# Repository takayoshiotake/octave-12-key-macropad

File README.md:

# Octave

[![CC BY-SA 4.0][cc-by-sa-shield]][cc-by-sa]

The Octave is a 12-key macropad.
It is primarily designed to be a compact keyboard with support for 12 function keys (F1 - F12).

## Status

- [x] prototype-3.1: Upgrade with LEDs under keys
  - [x] LED Animation
  - [x] PCB: OK!
- [x] prototype-3: Simple design
  - [x] Enclosure: OK!
  - [x] Test: OK!
  - [x] PCB: OK!
- [x] prototype-2: Custom MCU board
  - [x] Consideration
  - [x] Test
  - [x] PCB
- [x] prototype-1

## Specifications

- USB-C (USB2.0, HID)
  - 🔗 <https://pid.codes/1209/8CAE/>
- Hot-swap sockets for MX compatible switches
- Programmable firmware (CircuitPython)

## Layout

📄 [layout/keyboard-layout.png](layout/keyboard-layout.png) (rev.6)

- 12 function keys (F1 - F12)

**RAW data for Keyboard Layout Editor v0.15:**

📄 [layout/keyboard-layout.rawdata.json](layout/keyboard-layout.rawdata.json)

```json
[{f:3},"F1\nF9","F2\nF10","F3\nF11","F4\nF12"],
["F5\nVol-","F6\nVol+","F7\nRW","F8\nFF"],
["Shift","Ctrl","Esc\nLED","MO(1)"]
```

- 🔗 [Keyboard Layout Editor](http://www.keyboard-layout-editor.com/)

## Schematic

📄 [electronics/Octave_Input_PCB.svg](electronics/Octave_Input_PCB.svg) (rev.6.1.2)

I have also designed a custom MCU circuit from prototype-2, the MCU is RP2040 and the software runs on CircuitPython built specifically for it.

📄 [electronics/Octave_Input_PCB/Octave_Input_PCB.kicad_sch](electronics/Octave_Input_PCB/Octave_Input_PCB.kicad_sch)

### Upgrade schematic with LEDs under keys

📄 [electronics/Octave_Input_LED_PCB.svg](electronics/Octave_Input_LED_PCB.svg) (rev.1.0.0)

📄 [electronics/Octave_Input_PCB/Octave_Input_LED_PCB.kicad_sch](electronics/Octave_Input_PCB/Octave_Input_LED_PCB.kicad_sch)

## PCB

📄 [electronics/Octave_Input_PCB_3D.png](electronics/Octave_Input_PCB_3D.png) (rev.6.1.3)

📄 [electronics/Octave_Input_PCB/Octave_Input_PCB.kicad_pcb](electronics/Octave_Input_PCB/Octave_Input_PCB.kicad_pcb)

### Upgrade PCB with LEDs under keys

📄 [electronics/Octave_Input_LED_PCB_3D.png](electronics/Octave_Input_LED_PCB_3D.png) (rev.1.0.0)

📄 [electronics/Octave_Input_LED_PCB/Octave_Input_LED_PCB.kicad_pcb](electronics/Octave_Input_LED_PCB/Octave_Input_LED_PCB.kicad_pcb)

## CircuitPython

Software for the Octave (prototype-2, prototype-3) runs on CircuitPython.

**Latest:**

- 🔗 [adafruit/circuitpython](https://github.com/adafruit/circuitpython)
  - 🔗 <https://github.com/adafruit/circuitpython/tree/main/ports/raspberrypi/boards/takayoshiotake_octave_rp2040>
- 🔗 [Built UF2](https://adafruit-circuit-python.s3.amazonaws.com/index.html?prefix=bin/takayoshiotake_octave_rp2040/)

**Older:**

- 🔗 [takayoshiotake/circuitpython:7.3.x-board-octave-rp2040](https://github.com/takayoshiotake/circuitpython/tree/7.3.x-board-octave-rp2040)
  - 🔗 <https://github.com/takayoshiotake/circuitpython/tree/c3b4d05dc04d74c6229506215eae799fb23f37ce/ports/raspberrypi/boards/takayoshiotake_octave_rp2040>

- How to build:
  - 🔗 <https://learn.adafruit.com/building-circuitpython/build-circuitpython>
  - 🔗 <https://github.com/takayoshiotake/circuitpython/blob/c3b4d05dc04d74c6229506215eae799fb23f37ce/BUILDING.md>

## Plate

📄 [mechanics/Octave_Plate_3D.png](mechanics/Octave_Plate_3D.png) (rev.1.0.3)

📄 [mechanics/Octave_Plate/Octave_Plate.kicad_pcb](mechanics/Octave_Plate/Octave_Plate.kicad_pcb)

## Enclosure

- 📄 [mechanics/Octave_Enclosure-Case.stl](mechanics/Octave_Enclosure-Case.stl) (rev.1.0.0)
- 📄 [mechanics/Octave_Enclosure-Top Frame.stl](mechanics/Octave_Enclosure-Top%20Frame.stl) (rev.1.0.0)

## BOM & Software

🏷 [prototype-3-pcb](https://github.com/takayoshiotake/octave-12-key-macropad/releases/tag/prototype-3-pcb)

| Material | Unit | Designator | Note | JLCPCB Part # |
|-|-:|-|-|-|
| Octave CPU PCB rev.6.1.3 | 1 | n/a | JLCPCB |
| Octave Input PCB rev.6.1.3 *[2]* | 1 | n/a | JLCPCB |
| Octave Plate rev.1.0.3 | 1 | n/a | JLCPCB, Alminium PCB (t=1.6mm) |
| 0151660120 | 1 | n/a | Molex 0.50mm pitch FFC, Type D, 50.80mm, 12 circuits |
| CPG151101S11-2 | 12 | SW1-12 *[2]* | Kailh®︎ hot swap socket (White) |
||
| Octave Enclosure Case rev.1.0.0 | 1 | n/a | JLCPCB, 3D printing (MJF), PA12-HP Nylon |
| Octave Enclosure Top Frame rev.1.0.0 | 1 | n/a | JLCPCB, 3D printing (MJF), PA12-HP Nylon |
| PORON | 4 | n/a | 78mm x 2.5mm (t=1.5mm) |
| PORON | 4 | n/a | 59mm x 2.5mm (t=1.5mm) |
| Screw M2 5mm | 1 | n/a | Hirosugi B-0205 |
| Screw M2 8mm | 4 | n/a | Hirosugi B-0208 |
| Insert nut M2 | 4 | n/a | Hirosugi HSB-203030Z |
| Nut M2 | 1 | n/a | Hirosugi BNT-02-2 |
| Washer M2 | 1 | n/a | Hirosugi BW-0243-03 |
||
| 30pF 0402 | 2 | C15, C16 | PCBA | C1570 |
| 100nF 0402 | 10 | C5-14 | PCBA | C307331 |
| 1uF 0402 | 2 | C3, C4 | PCBA | C52923 |
| 10uF 0402 | 2 | C1, C2 | PCBA | C15525 |
| 1N4148WS | 12 | D1-12 *[2]* | PCBA | C2128 |
| HRO_TYPE-C-31-M-12 | 1 | J1 | PCBA, USB Connector (Type-C) | C165948 |
| JUSHUO_AFC01-S12FCC-00 | 2 | J2, J3 *[2]* | PCBA, FFC Connector (0.50mm pitch, 12 circuits) | C262268 |
| 27Ω 0402 | 2 | R3, R4 | PCBA | C352446 |
| 1KΩ 0402 | 2 | R7, R8 | PCBA | C11702 |
| 5.1KΩ 0402 | 2 | R1, R2 | PCBA | C25905 |
| 10KΩ 0402 | 2 | R5, R6 | PCBA | C25744 |
| AP2112K-3.3 | 1 | U1 | PCBA | C51118 |
| Raspberry Pi RP2040 | 1 | U2 | PCBA | C2040 |
| W25Q64JVSSIQ | 1 | U3 | PCBA | C179171 |
| 12MHz Crystal Resonator SMD-3225 | 1 | Y1 | PCBA, YSX221SL | C9002 |
| SKRPANE010 | 2 | SW21, SW22 | PCBA, Alps Alpine tactile switch | C470426 |
||
| WS2812C-2020-V1 | 1 | LED1 *[1]* | PCBA, NeoPixel | C2976072 |

MEMO: *[1]* To reduce costs, I did not assemble LED1 with PCBA.
MEMO: *[2]* Can be replaced with upgrade parts.

Upgrade parts:

| Material | Unit | Designator | Note | JLCPCB Part # |
|-|-:|-|-|-|
| Octave Input LED PCB rev.1.0.0 | 1 | n/a | JLCPCB |
| CPG151101S11-2 | 12 | SW1-12 | Kailh®︎ hot swap socket (White) |
||
| 1N4148WS | 12 | D1-12 | PCBA | C2128 |
| JUSHUO_AFC01-S12FCC-00 | 1 | J3 | PCBA, FFC Connector (0.50mm pitch, 12 circuits) | C262268 |
||
| WS2812B-Mini-V3 | 12 | LED201-0212 | NeoPixel |

- Octave CPU PCB rev.6.1.3, Octave Input PCB rev.6.1.3 (PCBA)

- Octave Input LED PCB rev.1.0.0 (Upgrade)

- Octave Plate rev.1.0.3

- Assembly

### Software

- [Software](software/README.md)

### History

- [[Closed] prototype-2](prototype-2/README.md)
- [[Closed] prototype-1](prototype-1/README.md)

## License

This work is licensed under a
[Creative Commons Attribution-ShareAlike 4.0 International License][cc-by-sa].

[![CC BY-SA 4.0][cc-by-sa-image]][cc-by-sa]

[cc-by-sa]: http://creativecommons.org/licenses/by-sa/4.0/
[cc-by-sa-image]: https://licensebuttons.net/l/by-sa/4.0/88x31.png
[cc-by-sa-shield]: https://img.shields.io/badge/license-CC%20BY--SA%204.0-lightgrey.svg

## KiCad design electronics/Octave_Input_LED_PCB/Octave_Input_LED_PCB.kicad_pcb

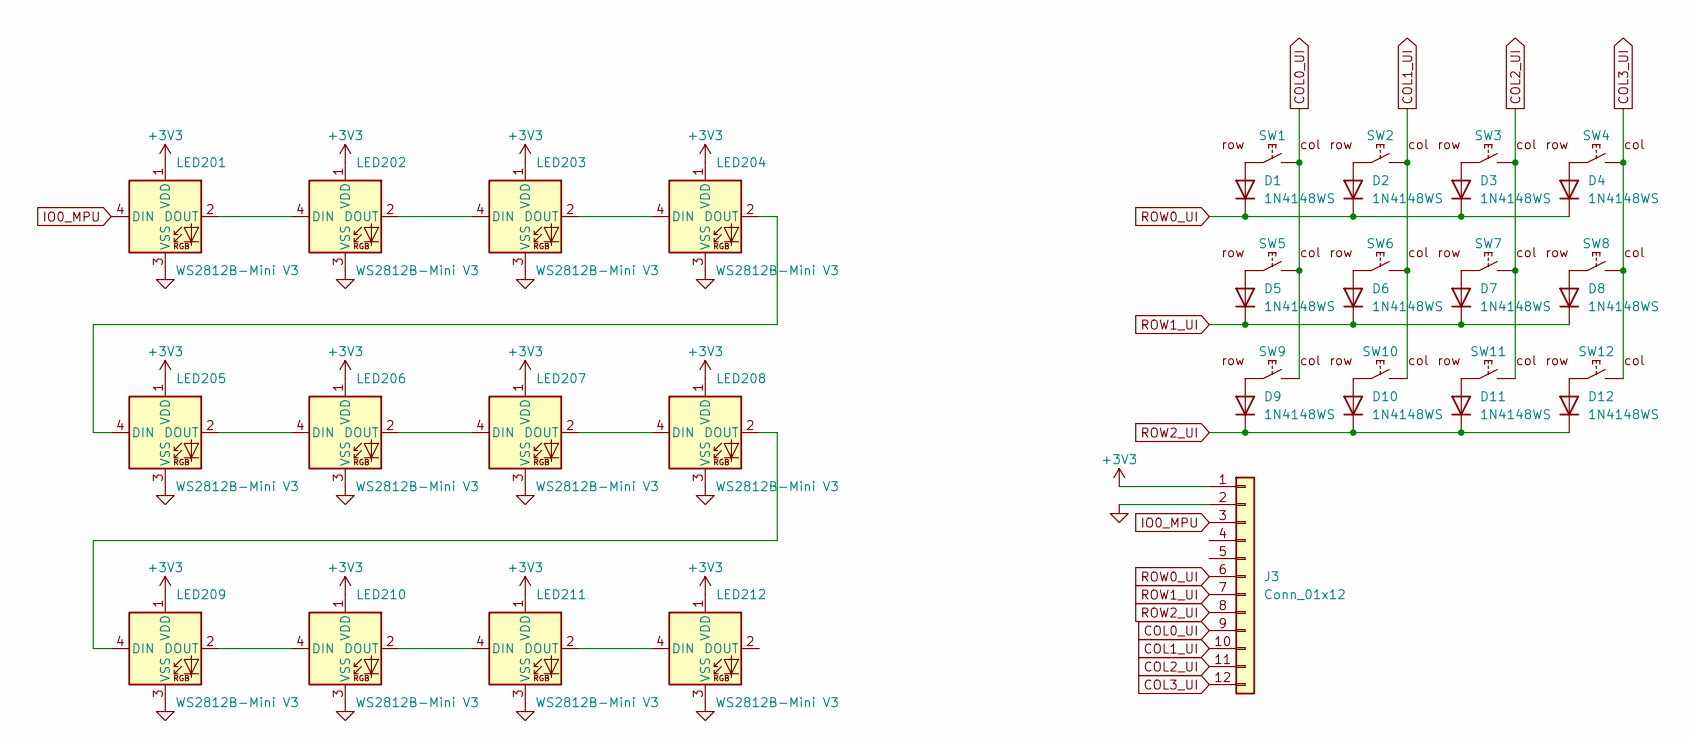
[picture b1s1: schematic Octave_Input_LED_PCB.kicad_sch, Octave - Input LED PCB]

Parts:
D1, D2, D3, D4, D5, D6, D7, D8, D9, D10, D11, D12: 1N4148WS; D_SOD-323F
J3: Conn_01x12; JUSHUO_AFC01-S12FCC-00
LED201, LED202, LED203, LED204, LED205, LED206, LED207, LED208, LED209, LED210, LED211, LED212: WS2812B-Mini V3; WS2812B-Mini_Inverted
SW1, SW2, SW3, SW4, SW5, SW6, SW7, SW8, SW9, SW10, SW11, SW12: SW_Hot_Swap_Socket; Hot_Swap_Socket_CPG151101S11

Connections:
+3V3: J3.1, LED201.1 (VDD), LED202.1 (VDD), LED203.1 (VDD), LED204.1 (VDD), LED205.1 (VDD), LED206.1 (VDD), LED207.1 (VDD), LED208.1 (VDD), LED209.1 (VDD), LED210.1 (VDD), LED211.1 (VDD), LED212.1 (VDD)
COL0_UI: J3.9, SW1.2, SW5.2, SW9.2
COL1_UI: J3.10, SW2.2, SW6.2, SW10.2
COL2_UI: J3.11, SW3.2, SW7.2, SW11.2
COL3_UI: J3.12, SW4.2, SW8.2, SW12.2
GND: J3.2, LED201.3 (VSS), LED202.3 (VSS), LED203.3 (VSS), LED204.3 (VSS), LED205.3 (VSS), LED206.3 (VSS), LED207.3 (VSS), LED208.3 (VSS), LED209.3 (VSS), LED210.3 (VSS), LED211.3 (VSS), LED212.3 (VSS)
IO0_MPU: J3.3, LED201.4 (DIN)
unnamed: D1.2 (A), SW1.1
unnamed: D2.2 (A), SW2.1
unnamed: D3.2 (A), SW3.1
unnamed: D4.2 (A), SW4.1
unnamed: D5.2 (A), SW5.1
unnamed: D6.2 (A), SW6.1
unnamed: D7.2 (A), SW7.1
unnamed: D8.2 (A), SW8.1
unnamed: D9.2 (A), SW9.1
unnamed: D10.2 (A), SW10.1
unnamed: D11.2 (A), SW11.1
unnamed: D12.2 (A), SW12.1
unnamed: LED201.2 (DOUT), LED202.4 (DIN)
unnamed: LED202.2 (DOUT), LED203.4 (DIN)
unnamed: LED203.2 (DOUT), LED204.4 (DIN)
unnamed: LED204.2 (DOUT), LED205.4 (DIN)
unnamed: LED205.2 (DOUT), LED206.4 (DIN)
unnamed: LED206.2 (DOUT), LED207.4 (DIN)
unnamed: LED207.2 (DOUT), LED208.4 (DIN)
unnamed: LED208.2 (DOUT), LED209.4 (DIN)
unnamed: LED209.2 (DOUT), LED210.4 (DIN)
unnamed: LED210.2 (DOUT), LED211.4 (DIN)
unnamed: LED211.2 (DOUT), LED212.4 (DIN)
ROW0_UI: D1.1 (K), D2.1 (K), D3.1 (K), D4.1 (K), J3.6
ROW1_UI: D5.1 (K), D6.1 (K), D7.1 (K), D8.1 (K), J3.7
ROW2_UI: D9.1 (K), D10.1 (K), D11.1 (K), D12.1 (K), J3.8

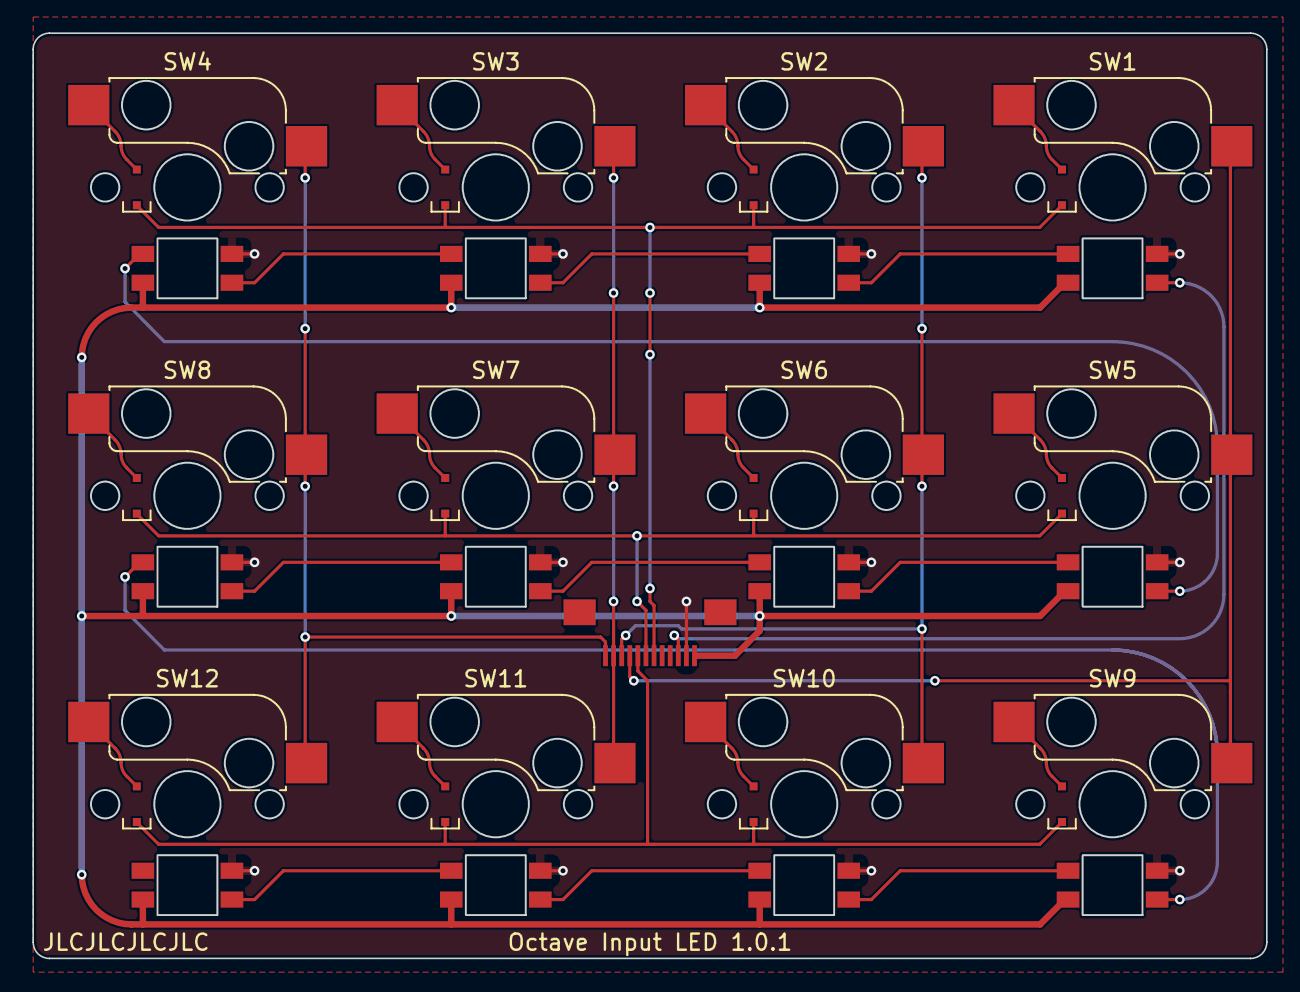
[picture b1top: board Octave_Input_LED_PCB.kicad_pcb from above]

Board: 2 copper layers, 76.2 x 57.2 mm, 37 parts (0 on the bottom side), 33 nets.

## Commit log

2022-02-23 Update Specifications and Layout
2022-02-23 Create LICENSE
2022-02-23 Study key matrix
2022-02-26 New add KiCad project to prepare footprints
2022-02-26 Add hot swap socket footprint
2022-02-27 Update Hot_Swap_Socket_CPG151101S11.scad
    Modify pin height
2022-02-27 Add hot swap socket 3D shape
2022-02-27 Pin my KiCad library to the project
2022-02-28 Add hot swap socket symbol
2022-03-02 New add KiCad project
2022-03-02 Add key matrix schematic
2022-03-02 Connect D
2022-03-02 Update schematic and PCB
2022-03-02 Create incremental encoder footprint
2022-03-05 Update schematic
2022-03-06 Schematic rev.1 is available
2022-03-06 Fix svg background color
2022-03-06 Reset PCB tracks
2022-03-06 Update PCB tracks
2022-03-06 Update schematic
    Since label C hid GND in the net list, remove label C and simply connect to GND.
2022-03-06 Update PCB
2022-03-09 Add PCB 3D image
2022-03-21 Add enclosure 3D model (Base only)
2022-03-21 Update enclosure 3D model
    Modify base, and add cover
2022-03-28 Update PCB 3D image
2022-03-28 Add prototype info
2022-03-29 Update prototype info
2022-03-29 Add first prototype software, test SW14
2022-03-30 Add key-matrix scanning
2022-03-30 Change the height of the enclosure base to fit the USB cable
2022-04-02 Add knob rotation direction detection
2022-04-02 Update prototype issues
2022-04-02 Improve knob rotation direction detection
2022-04-08 Refactor prototype software
2022-04-08 Add: Assign rotary encoder operation to mouse wheel operation
2022-04-08 Add: Disable USB drive if SW14 is not pressed at startup
2022-04-09 Format markdown
2022-04-09 Update NOTE
2022-04-10 Add prototype enclosure
2022-04-10 Add function-keys press-release event
2022-04-10 Change key map (prototype)
2022-04-13 Update schematic
    Close some issues:
    - Fix U1 symbol
    - Change R1 and R3 value
2022-04-14 Add RP2040 footprint
2022-04-14 Fix pin assignment of RP2040 footprint
2022-04-15 Close first prototype, start second prototype
2022-04-17 Change layout
    Swap the MO and knob and add a stick controller
2022-04-28 Add stick controller symbol
2022-04-30 [WIP] Update schematic
2022-05-04 Add RP2040 #schematic
2022-05-05 Renumber the capacitors #schematic
2022-05-05 Change the diode footprint for the key matrix from SOD-323 to SOD-323F
2022-05-06 Improve hot swap socket footprint
2022-05-06 [WIP] Update schematic and PCB
2022-05-06 Improve footprint
2022-05-06 Rename usb c footprint
2022-05-06 [WIP] Update schematic and PCB
    Add a USB-C connector, but using the Molex 1054500101 makes routing very difficult.
2022-05-07 Change the USB-C connector to HRO TYPE-C-31-M-12
2022-05-14 [WIP] Update PCB
2022-05-17 Add crystal resonator
2022-05-23 [WIP]
2022-05-29 Complete schematic and PCB (rev.5.0.0)
2022-05-30 Fix C13 and C14 value, improve Y1 pattern
2022-05-30 Add pull-up for QSPI_SS_N
2022-05-30 Change C1 and C2 value
2022-05-30 Rename footprint of tactile switch
2022-06-13 Oops, fix schematics of SW21 and SW22
2022-06-13 Improve schematic and PCB
2022-06-14 Update prototype-2 info
2022-06-14 Clean up directories
2022-06-16 Add link to CircuitPython
2022-06-18 Add BOM of PCB
2022-06-19 Add a link to the CircuitPython 7.3.x code
2022-06-19 [WIP] Add software for prototype-2
2022-06-19 Add a link to the protoype-2-pcb tag
2022-06-19 Add a issue of prototype-2 (solved)
2022-06-19 Add an issue of prototype-2 (solved)
2022-06-19 Support mouse buttons
2022-06-19 Add mouse moving by stick controller
2022-07-31 Add prototype-2 issues
2022-08-12 Update README.md
    Update the link to latest CircuitPython
2022-08-20 Update README.md
    Move prototype-2 info
2022-08-20 Complete prototype-2
2022-08-23 Change specs and layout for simplicity
2022-09-10 Remove unused symbols on schematic
2022-09-11 Separate the PCB into two parts: UI and MPU
2023-01-03 Update Octave_Input_PCB.kicad_pcb
    Adjust clearance
2023-01-07 Add plate design
2023-01-08 Update plate design
2023-01-08 Fix Edge.Cuts of PCB
2023-01-08 Fix footprint of J2 and J3
2023-01-09 Change plate design
2023-01-09 Modify PCB and plate
2023-01-22 [WIP] Test prototype-3
2023-01-22 Update BOM for prototype-3
2023-01-22 Fix BOM for prototype-2
2023-01-22 Add circuitpython-bin
2023-01-22 Fix link to bin
2023-01-22 Add photo of prototype-3
2023-01-22 Update software for prototype-3
2023-01-22 Customize key bindings for testing prototype-3
2023-01-22 Add lib
2023-01-23 Remove old enclosure design
2023-02-11 Add enclosure photo and stl files of it
2023-02-11 Update BOM
2023-02-11 Complete prototype-3
2023-02-11 Change keymap
2023-02-26 Change FFC jumper 0151660122 to 0151660120 of just the right length
2023-02-26 Update the version of CircuitPython used to 8.0.3
    Update software dependencies
2023-02-26 Modify keyboard layout to match current situation
2023-02-26 Modify vid and pid of settings.json
2023-02-26 Add link to vid and pid
2023-03-11 Update keyboard layout
2023-03-16 Create KiCad project for LEDs under keys by copying Input PCB
2023-03-16 Remove CPU PCB from Input LED PCB
2023-03-16 Add footprint of WS2812B-Mini with inverted placement
2023-03-19 Improve edge cuts of WS2812B-Mini (Inverted)
2023-03-19 Route PCB
2023-03-21 Add 3D image of the upgrade PCB
2023-03-21 Add schematic image of the upgrade PCB
2023-03-21 Modify background color of the upgrade PCB schematic SVG image
2023-03-21 Wait for my PCB ordered
2023-04-01 Update info about LED PCB (Upgrade parts)
2023-04-01 Add RGB lights
2023-04-02 Change color
2023-04-05 Add led animation pattern
2023-04-09 Improve footprint of WS2812B-Mini_Inverted
2023-04-09 Add LEDs animation
2024-03-06 Update LICENSE
